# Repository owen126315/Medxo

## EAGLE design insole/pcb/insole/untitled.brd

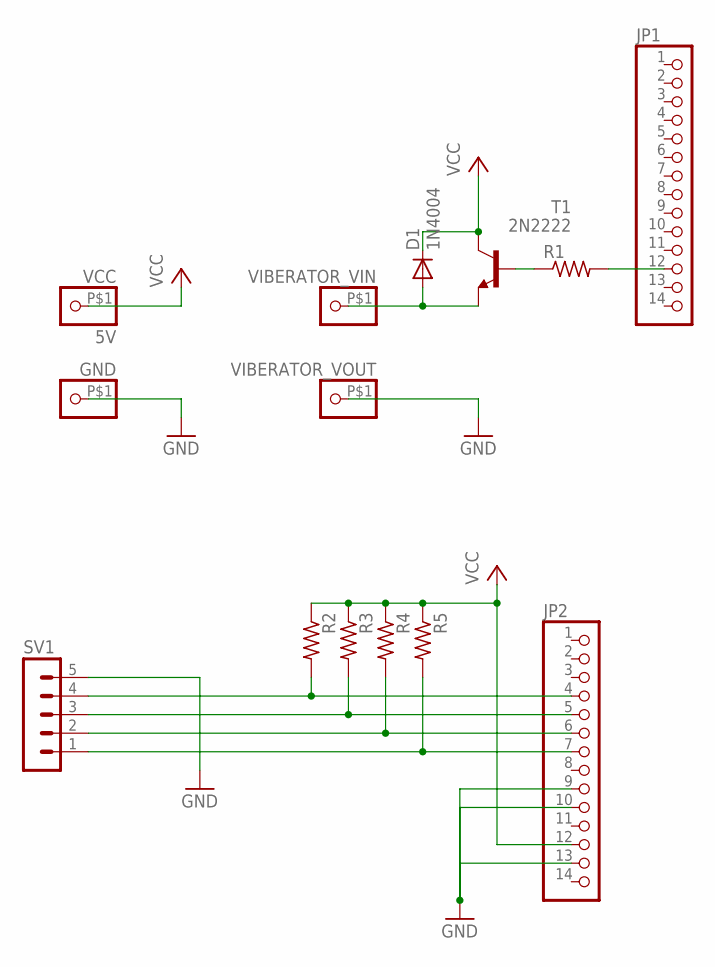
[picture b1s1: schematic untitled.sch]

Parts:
D1: 1N4004; DO41-10
GND: PINHD-1X1-BIGPOGO; 1X1-BIGPOGO
JP1, JP2: PINHD-1X14-CB; 1X14-CB
R1, R2, R3, R4, R5: R-US_R0805; R0805
SV1: MA05-1
T1: 2N2222; TO92-EBC-OVAL
VCC: 5V; 1X1-BIGPOGO
VIBERATOR_VIN: PINHD-1X1-BIGPOGO; 1X1-BIGPOGO
VIBERATOR_VOUT: PINHD-1X1-BIGPOGO; 1X1-BIGPOGO

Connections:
GND: GND.P$1, JP2.9, JP2.10, JP2.13, SV1.5, VIBERATOR_VOUT.P$1
unnamed: R1.1, T1.B
unnamed: JP1.12, R1.2
unnamed: JP2.7, R5.2, SV1.1
unnamed: JP2.6, R4.2, SV1.2
unnamed: JP2.5, R3.2, SV1.3
unnamed: JP2.4, R2.2, SV1.4
unnamed: D1.A, T1.E, VIBERATOR_VIN.P$1
VCC: D1.C, JP2.12, R2.1, R3.1, R4.1, R5.1, T1.C, VCC.P$1

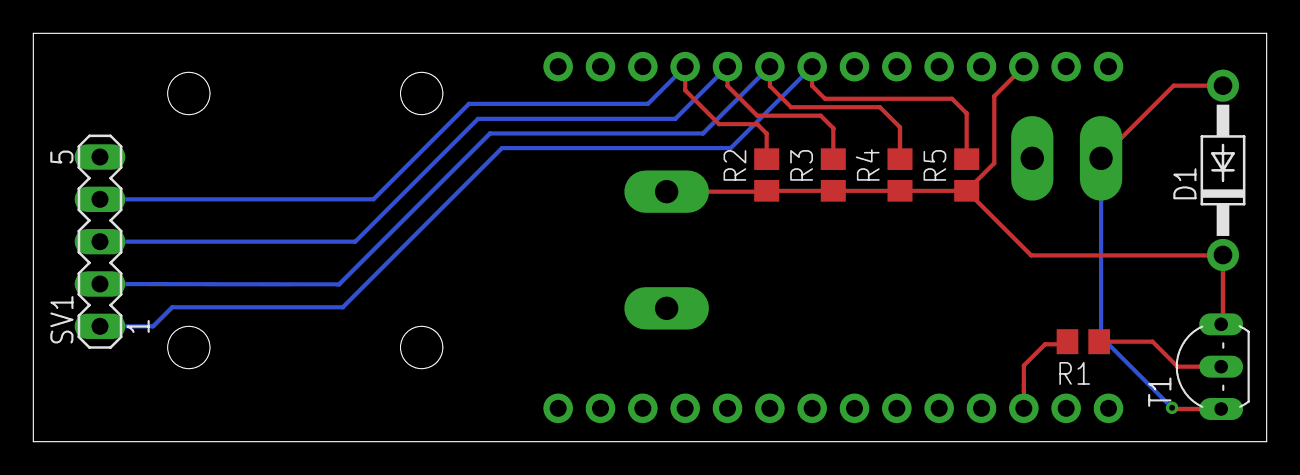
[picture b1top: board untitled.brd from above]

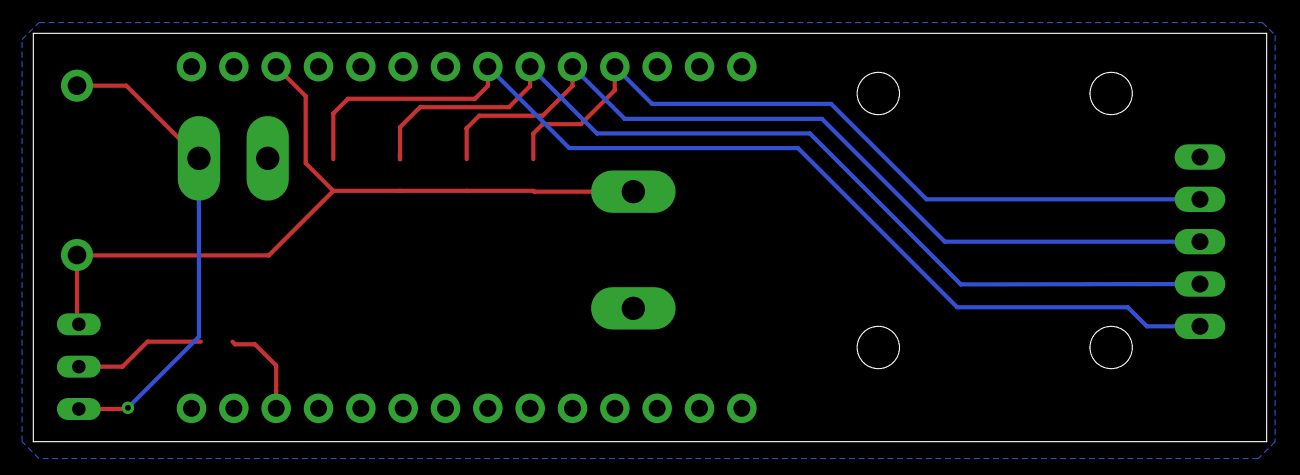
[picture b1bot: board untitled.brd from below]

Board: 2 copper layers, 74.0 x 24.5 mm, 14 parts (2 on the bottom side), 9 nets.

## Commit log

2018-09-12 done
